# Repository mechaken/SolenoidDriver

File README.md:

# SolenoidDriver

### 表

### 裏

## 概要
独自にピン定義したPCIeを使ったソレノイド駆動回路です。

最大17個のソレノイドを接続と駆動ができます。(17個も駆動させない場合は、A-Cのうち使用する行に接続されているダーリントントランジスタやその他部品のみ実装し、動作させることも可能です。)

作成しているモータードライバ([CAN-H-Bridge_Solo_MD](https://github.com/picopicodevil/CAN_H-Bridge_Solo_MD))とほぼ同じ大きさなので、同一のマザーボードの中にモータードライバと本基板を入れることが可能です。

## 機能
- CAN通信を用いたソレノイドの制御
- DIPスイッチを利用して、同じプログラムで同一CANバスに最大4つ搭載可能
- ディジタルアイソレータを用いた制御-駆動電源の分離

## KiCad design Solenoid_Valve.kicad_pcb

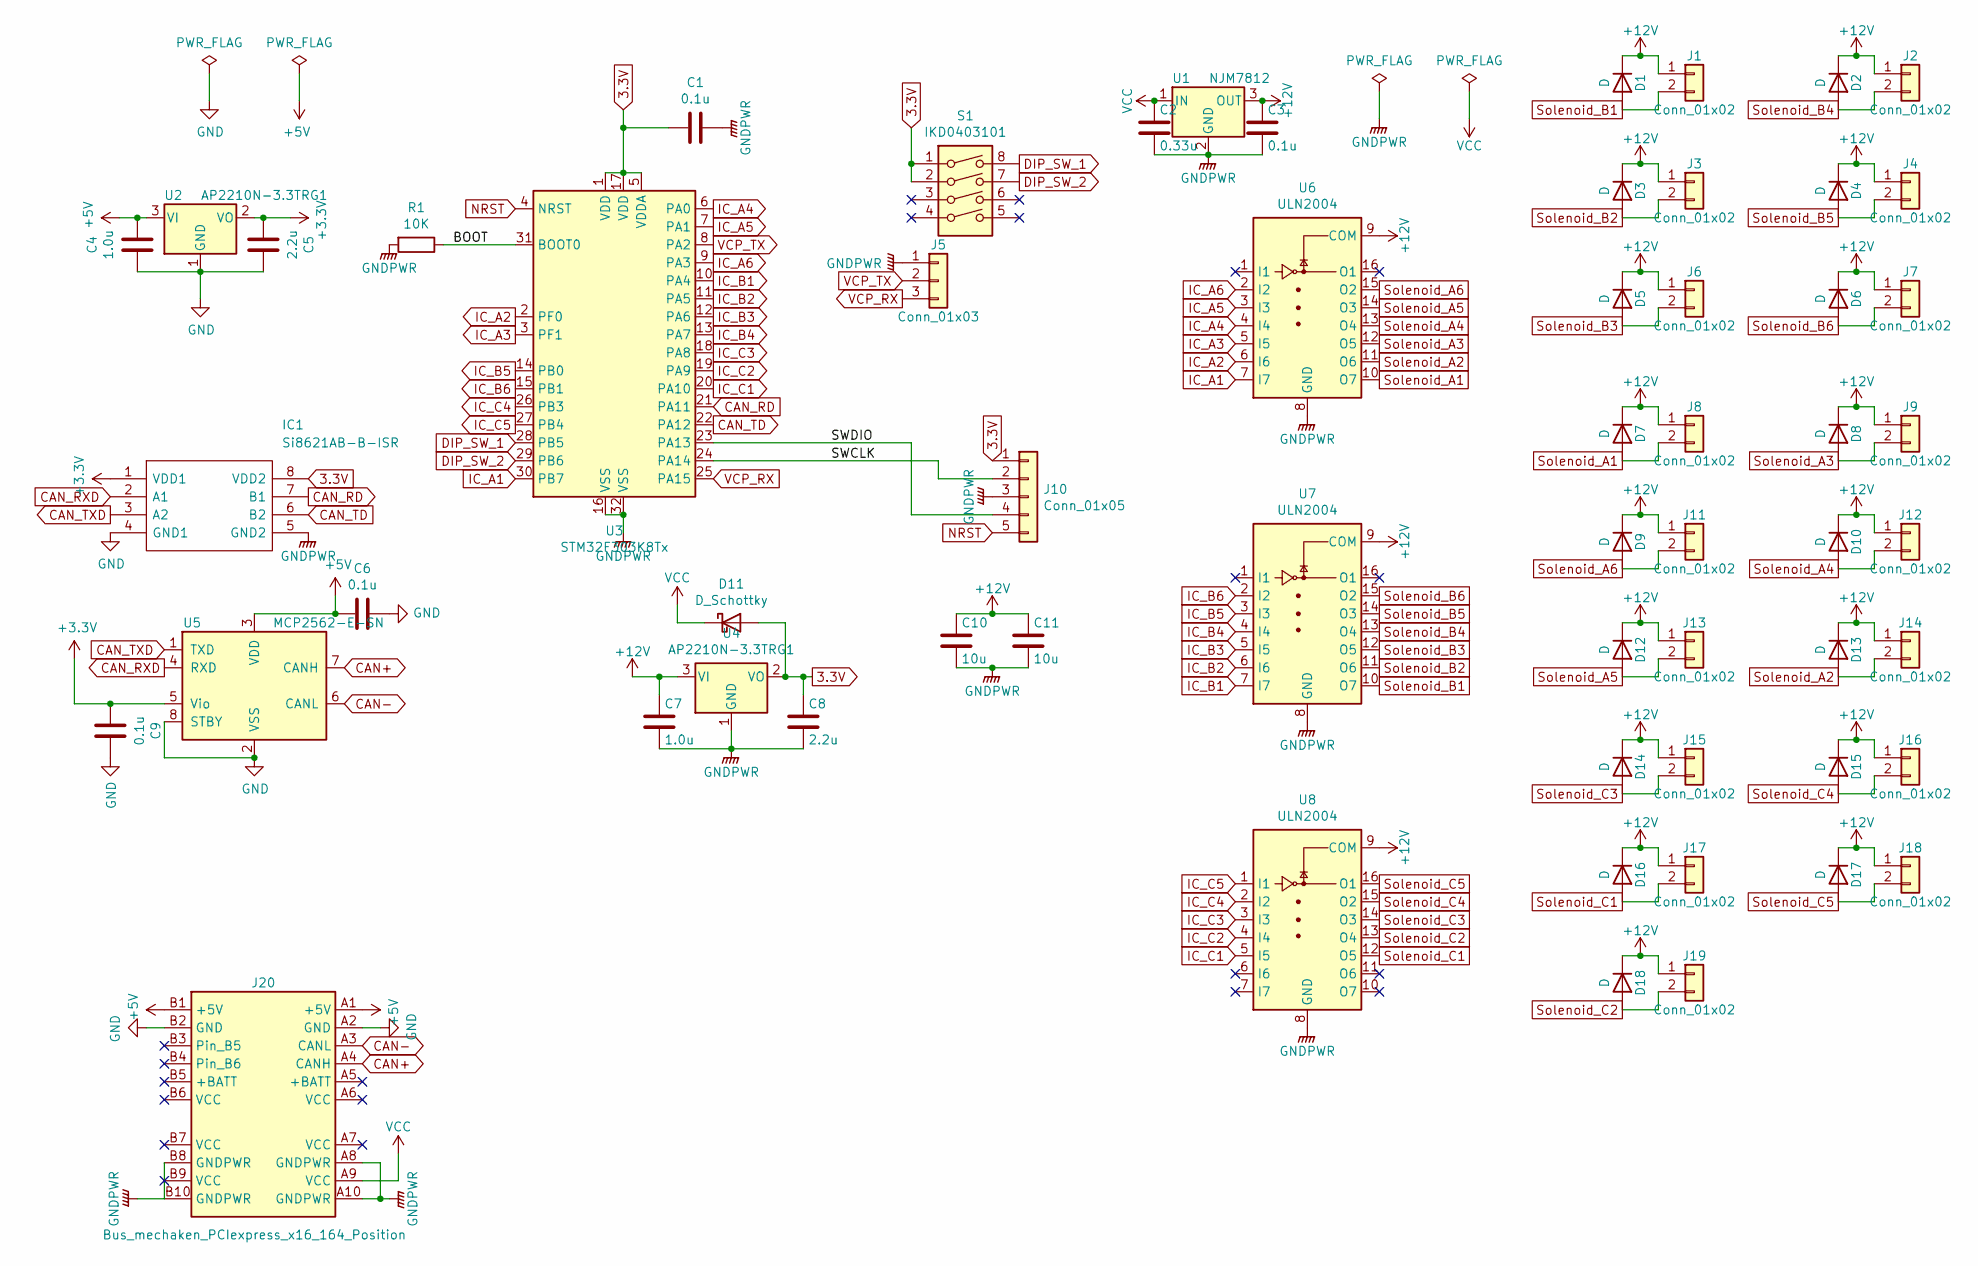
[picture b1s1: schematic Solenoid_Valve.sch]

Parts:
C1, C3, C6, C9: 0.1u; C_0805_2012Metric_Pad1.18x1.45mm_HandSolder
C2: 0.33u; C_0805_2012Metric_Pad1.18x1.45mm_HandSolder
C4, C7: 1.0u; C_0805_2012Metric_Pad1.18x1.45mm_HandSolder
C5, C8: 2.2u; C_0805_2012Metric_Pad1.18x1.45mm_HandSolder
C10, C11: 10u; C_0805_2012Metric_Pad1.18x1.45mm_HandSolder
D1, D2, D3, D4, D5, D6, D7, D8, D9, D10, D12, D13, D14, D15, D16, D17, D18: D; D_2010_5025Metric_Pad1.52x2.65mm_HandSolder
D11: D_Schottky; D_0603_1608Metric_Pad1.05x0.95mm_HandSolder
IC1: Si8621AB-B-ISR; SOIC127P600X175-8N; Mouser Part Number 634-SI8621AB-B-ISR
J1, J2, J3, J4, J6, J7, J8, J9, J11, J12, J13, J14, J15, J16, J17, J18, J19: Conn_01x02; JST_XH_B2B-XH-A_1x02_P2.50mm_Vertical
J5: Conn_01x03; PinHeader_1x03_P2.54mm_Vertical
J10: Conn_01x05; PinHeader_1x05_P2.54mm_Vertical
J20: Bus_mechaken_PCIexpress_x16_164_Position; BUS_mechaken_PCIexpress_x16
R1: 10K; R_0603_1608Metric_Pad0.98x0.95mm_HandSolder
S1: IKD0403101; DIP-8_W7.62mm
U1: NJM7812; TO-252-2
U2, U4: AP2210N-3.3TRG1; SOT-23_Handsoldering
U3: STM32F303K8Tx; LQFP-32_7x7mm_P0.8mm
U5: MCP2562-E-SN; SOIC-8_3.9x4.9mm_P1.27mm
U6, U7, U8: ULN2004; SOIC-16_3.9x9.9mm_P1.27mm

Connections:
3.3V: C1.2, C8.1, D11.2 (A), IC1.8 (VDD2), J10.1, S1.1, S1.2, U3.1 (VDD), U3.5 (VDDA), U3.17 (VDD), U4.2 (VO)
+3V3: C5.2, C9.2, IC1.1 (VDD1), U2.2 (VO), U5.5 (Vio)
+5V: C4.1, C6.2, J20.A1 (+5V), J20.B1 (+5V), U2.3 (VI), U5.3 (VDD)
+12V: C3.1, C7.1, C10.1, C11.1, D1.1 (K), D2.1 (K), D3.1 (K), D4.1 (K), D5.1 (K), D6.1 (K), D7.1 (K), D8.1 (K), D9.1 (K), D10.1 (K), D12.1 (K), D13.1 (K), D14.1 (K), D15.1 (K), D16.1 (K), D17.1 (K), D18.1 (K), J1.1, J2.1, J3.1, J4.1, J6.1, J7.1, J8.1, J9.1, J11.1, J12.1, J13.1, J14.1, J15.1, J16.1, J17.1, J18.1, J19.1, U1.3 (OUT), U4.3 (VI), U6.9 (COM), U7.9 (COM), U8.9 (COM)
/BOOT: R1.1, U3.31 (BOOT0)
/SWCLK: J10.2, U3.24 (PA14)
/SWDIO: J10.4, U3.23 (PA13)
CAN+: J20.A4 (CANH), U5.7 (CANH)
CAN-: J20.A3 (CANL), U5.6 (CANL)
CAN_RD: IC1.7 (B1), U3.21 (PA11)
CAN_RXD: IC1.2 (A1), U5.4 (RXD)
CAN_TD: IC1.6 (B2), U3.22 (PA12)
CAN_TXD: IC1.3 (A2), U5.1 (TXD)
DIP_SW_1: S1.8, U3.28 (PB5)
DIP_SW_2: S1.7, U3.29 (PB6)
GND: C4.2, C5.1, C6.1, C9.1, IC1.4 (GND1), J20.A2 (GND), J20.B2 (GND), U2.1 (GND), U5.2 (VSS), U5.8 (STBY)
GNDPWR: C1.1, C2.2, C3.2, C7.2, C8.2, C10.2, C11.2, IC1.5 (GND2), J5.1, J10.3, J20.A8 (GNDPWR), J20.A10 (GNDPWR), J20.B8 (GNDPWR), J20.B10 (GNDPWR), R1.2, U1.2 (GND), U3.16 (VSS), U3.32 (VSS), U4.1 (GND), U6.8 (GND), U7.8 (GND), U8.8 (GND)
IC_A1: U3.30 (PB7), U6.7 (I7)
IC_A2: U3.2 (PF0), U6.6 (I6)
IC_A3: U3.3 (PF1), U6.5 (I5)
IC_A4: U3.6 (PA0), U6.4 (I4)
IC_A5: U3.7 (PA1), U6.3 (I3)
IC_A6: U3.9 (PA3), U6.2 (I2)
IC_B1: U3.10 (PA4), U7.7 (I7)
IC_B2: U3.11 (PA5), U7.6 (I6)
IC_B3: U3.12 (PA6), U7.5 (I5)
IC_B4: U3.13 (PA7), U7.4 (I4)
IC_B5: U3.14 (PB0), U7.3 (I3)
IC_B6: U3.15 (PB1), U7.2 (I2)
IC_C1: U3.20 (PA10), U8.5 (I5)
IC_C2: U3.19 (PA9), U8.4 (I4)
IC_C3: U3.18 (PA8), U8.3 (I3)
IC_C4: U3.26 (PB3), U8.2 (I2)
IC_C5: U3.27 (PB4), U8.1 (I1)
NRST: J10.5, U3.4 (NRST)
Solenoid_A1: D7.2 (A), J8.2, U6.10 (O7)
Solenoid_A2: D13.2 (A), J14.2, U6.11 (O6)
Solenoid_A3: D8.2 (A), J9.2, U6.12 (O5)
Solenoid_A4: D10.2 (A), J12.2, U6.13 (O4)
Solenoid_A5: D12.2 (A), J13.2, U6.14 (O3)
Solenoid_A6: D9.2 (A), J11.2, U6.15 (O2)
Solenoid_B1: D1.2 (A), J1.2, U7.10 (O7)
Solenoid_B2: D3.2 (A), J3.2, U7.11 (O6)
Solenoid_B3: D5.2 (A), J6.2, U7.12 (O5)
Solenoid_B4: D2.2 (A), J2.2, U7.13 (O4)
Solenoid_B5: D4.2 (A), J4.2, U7.14 (O3)
Solenoid_B6: D6.2 (A), J7.2, U7.15 (O2)
Solenoid_C1: D16.2 (A), J17.2, U8.12 (O5)
Solenoid_C2: D18.2 (A), J19.2, U8.13 (O4)
Solenoid_C3: D14.2 (A), J15.2, U8.14 (O3)
Solenoid_C4: D15.2 (A), J16.2, U8.15 (O2)
Solenoid_C5: D17.2 (A), J18.2, U8.16 (O1)
VCC: C2.1, D11.1 (K), J20.A9 (VCC), U1.1 (IN)
VCP_RX: J5.3, U3.25 (PA15)
VCP_TX: J5.2, U3.8 (PA2)

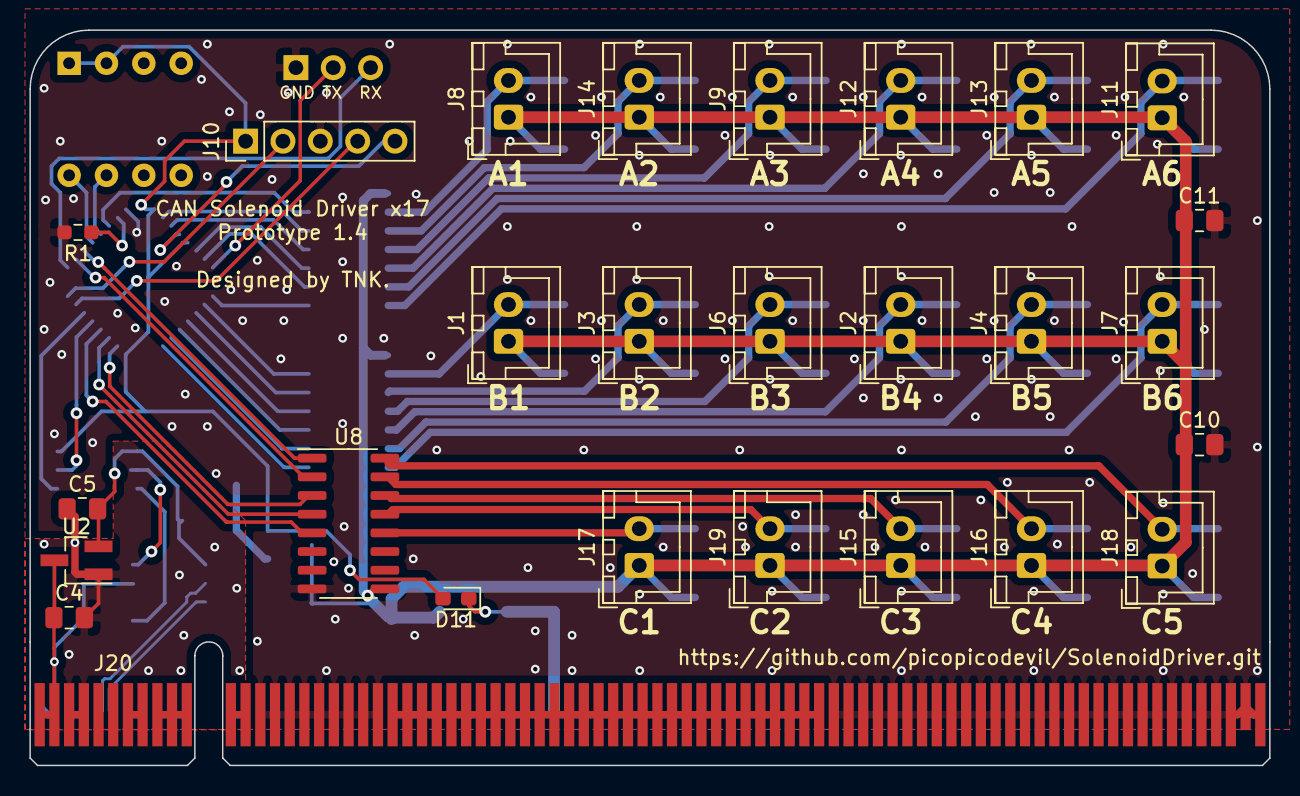
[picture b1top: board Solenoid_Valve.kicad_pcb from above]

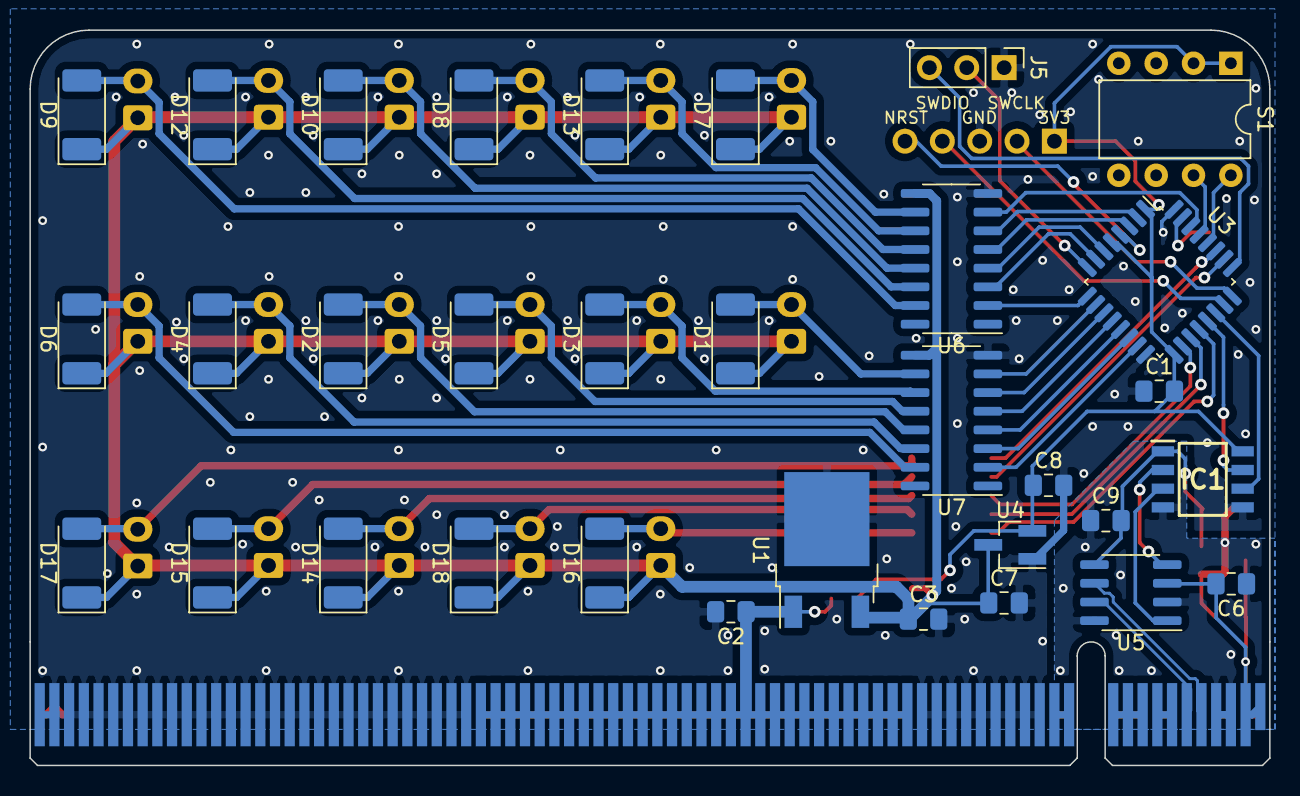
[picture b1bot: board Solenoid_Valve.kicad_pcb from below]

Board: 2 copper layers, 84.3 x 50.0 mm, 60 parts (33 on the bottom side), 55 nets.

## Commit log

2019-12-07 Prototype
2019-12-24 change
    Remove NRST SW
    clean
2019-12-27 Prototype-1.1
2020-01-19 fix
    ST-LINK部分の配線を修正
2020-02-21 fix
    BOOT0の配線を修正
2020-03-04 change
    フットプリントを手はんだ用に変更
    レギュレーター保護用のダイオードを追加
2020-03-04 Release
    ガーバーファイルを出力
2020-06-21 Release
    Prototype-1.3をリリース
2020-06-21 .gitignore is now working
2020-11-03 Update: フットプリントライブラリの変更
2020-11-06 Fix: Symbol & Footprint Library
2020-11-07 Delete: ガーバーファイルを削除
2020-11-07 Delete: 余分なファイルを削除
2020-11-07 Delete: pcb-bak
2020-11-07 Delete: ガーバーファイル
2020-11-21 Update: ダーリントントランジスタアレイをULN2003に変更
2021-09-20 Remove: 発注用ファイルを削除
2021-09-20 Update: IC1の3Dモデルを設定
2021-09-20 Update: READMEを加筆
2021-09-20 Update: KiCadのバージョンが変更
2021-09-24 Create LICENSE
